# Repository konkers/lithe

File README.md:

# lithe
A joystick/game controller firmware.

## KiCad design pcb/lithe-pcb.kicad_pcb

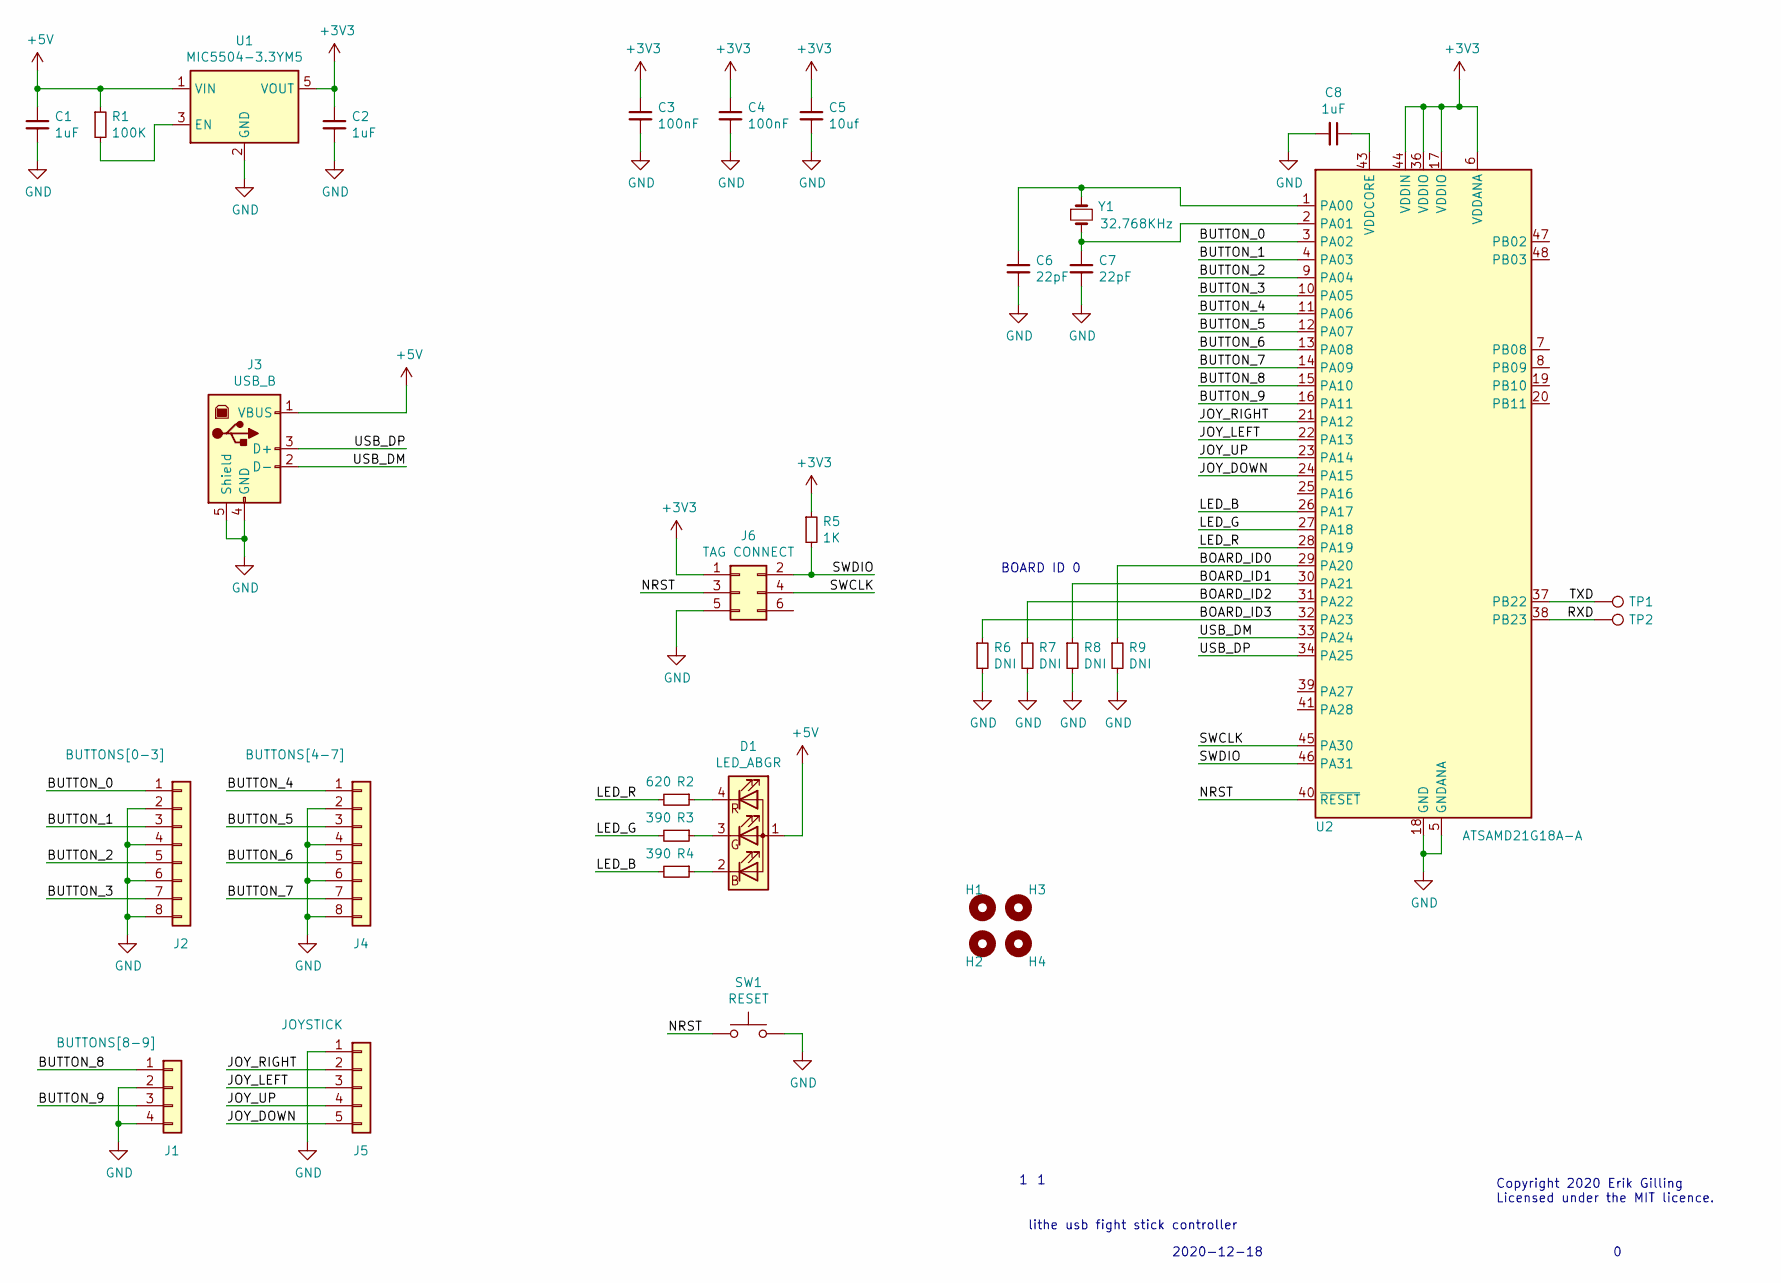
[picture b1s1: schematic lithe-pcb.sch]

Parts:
C1, C2, C8: 1uF; C_0402_1005Metric; DIGI_PN 1276-6524-2-ND
C3, C4: 100nF; C_0402_1005Metric; DIGI_PN 311-2077-1-ND
C5: 10uf; C_0603_1608Metric; DIGI_PN 490-3298-1-ND
C6, C7: 22pF; C_0402_1005Metric; DIGI_PN 445-1239-1-ND
D1: LED_ABGR; LED_Cree-PLCC4_2x2mm_CW; DIGI_PN CLMVC-FKA-CL1D1L71BB7C3C3TR-ND
H1, H2, H3, H4: MountingHole; MountingHole_3.2mm_M3_ISO7380
J1: BUTTONS[8-9]; PhoenixContact_MCV_1,5_4-G-3.5_1x04_P3.50mm_Vertical; DIGI_PN 277-5738-ND
J2: BUTTONS[0-3]; PhoenixContact_MCV_1,5_8-G-3.5_1x08_P3.50mm_Vertical; DIGI_PN 277-5759-ND
J3: USB_B; USB_B_Lumberg_2411_02_Horizontal
J4: BUTTONS[4-7]; PhoenixContact_MCV_1,5_8-G-3.5_1x08_P3.50mm_Vertical; DIGI_PN 277-5759-ND
J5: JOYSTICK; PhoenixContact_MCV_1,5_5-G-3.5_1x05_P3.50mm_Vertical; DIGI_PN 277-5752-ND
J6: TAG CONNECT; Tag-Connect_TC2030-IDC-NL_2x03_P1.27mm_Vertical
R1: 100K; R_0402_1005Metric; DIGI_PN YAG2307TR-ND
R2: 620; R_0402_1005Metric; DIGI_PN 311-620LRTR-ND
R3, R4: 390; R_0402_1005Metric; DIGI_PN 311-390LRTR-ND
R5: 1K; R_0402_1005Metric; DIGI_PN 311-1.00KLRTR-ND
R6, R7, R8, R9: DNI; R_0402_1005Metric; DIGI_PN 311-0.0JRTR-ND
SW1: RESET; SW_SPST_EVQPE1; DIGI_PN CKN12311-2-ND
TP1, TP2: TestPoint; TestPoint_Pad_D1.0mm
U1: MIC5504-3.3YM5; SOT-23-5; DIGI_PN MIC5504-3.3YM5-T5TR-ND
U2: ATSAMD21G18A-A; TQFP-48_7x7mm_P0.5mm; DIGI_PN ATSAMD21G18A-AU-ND
Y1: 32.768KHz; Crystal_SMD_MicroCrystal_CC7V-T1A-2Pin_3.2x1.5mm_HandSolder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; DIGI_PN 2195-CM7VT1ALOWESR32.768KHZ12.5PF20TAQC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

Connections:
+3V3: C2.1, C3.1, C4.1, C5.1, J6.1, R5.1, U1.5 (VOUT), U2.6 (VDDANA), U2.17 (VDDIO), U2.36 (VDDIO), U2.44 (VDDIN)
+5V: C1.1, D1.1 (A), J3.1 (VBUS), R1.1, U1.1 (VIN)
/BOARD_ID0: R9.1, U2.29 (PA20)
/BOARD_ID1: R8.1, U2.30 (PA21)
/BOARD_ID2: R7.1, U2.31 (PA22)
/BOARD_ID3: R6.1, U2.32 (PA23)
/BUTTON_0: J2.1, U2.3 (PA02)
/BUTTON_1: J2.3, U2.4 (PA03)
/BUTTON_2: J2.5, U2.9 (PA04)
/BUTTON_3: J2.7, U2.10 (PA05)
/BUTTON_4: J4.1, U2.11 (PA06)
/BUTTON_5: J4.3, U2.12 (PA07)
/BUTTON_6: J4.5, U2.13 (PA08)
/BUTTON_7: J4.7, U2.14 (PA09)
/BUTTON_8: J1.1, U2.15 (PA10)
/BUTTON_9: J1.3, U2.16 (PA11)
/JOY_DOWN: J5.5, U2.24 (PA15)
/JOY_LEFT: J5.3, U2.22 (PA13)
/JOY_RIGHT: J5.2, U2.21 (PA12)
/JOY_UP: J5.4, U2.23 (PA14)
/LED_B: R4.2, U2.26 (PA17)
/LED_G: R3.2, U2.27 (PA18)
/LED_R: R2.2, U2.28 (PA19)
/NRST: J6.3, SW1.1, U2.40 (~RESET)
/RXD: TP2.1, U2.38 (PB23)
/SWCLK: J6.4, U2.45 (PA30)
/SWDIO: J6.2, R5.2, U2.46 (PA31)
/TXD: TP1.1, U2.37 (PB22)
/USB_DM: J3.2 (D-), U2.33 (PA24)
/USB_DP: J3.3 (D+), U2.34 (PA25)
GND: C1.2, C2.2, C3.2, C4.2, C5.2, C6.2, C7.2, C8.2, J1.2, J1.4, J2.2, J2.4, J2.6, J2.8, J3.4 (GND), J3.5 (Shield), J4.2, J4.4, J4.6, J4.8, J5.1, J6.5, R6.2, R7.2, R8.2, R9.2, SW1.2, U1.2 (GND), U2.5 (GNDANA), U2.18 (GND), U2.35 (GND), U2.42 (GND)
unnamed: C6.1, U2.1 (PA00), Y1.1
unnamed: C7.1, U2.2 (PA01), Y1.2
unnamed: C8.1, U2.43 (VDDCORE)
unnamed: D1.2 (BK), R4.1
unnamed: D1.3 (GK), R3.1
unnamed: D1.4 (RK), R2.1
unnamed: R1.2, U1.3 (EN)

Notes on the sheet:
lithe usb fight stick controller
2020-12-18
Copyright 2020 Erik Gilling Licensed under the MIT licence.
BOARD ID 0

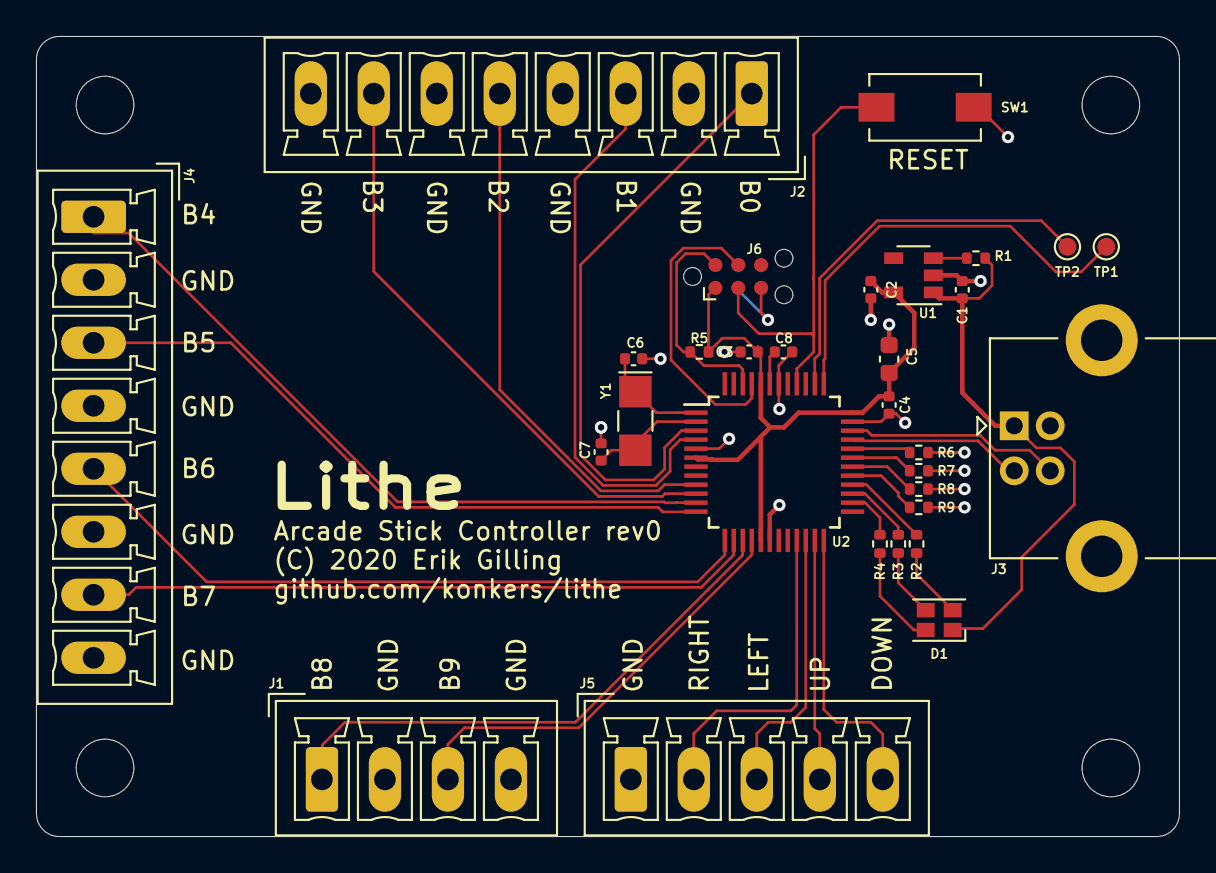
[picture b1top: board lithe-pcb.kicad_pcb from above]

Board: 2 copper layers, 63.5 x 44.5 mm, 34 parts (0 on the bottom side), 38 nets.

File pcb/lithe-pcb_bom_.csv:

Component,Description,Part,References,Value,Footprint,Quantity Per PCB,Datasheet,DIGI_PN
1,"Unpolarized capacitor, small symbol",C_Small,C6 C7,22pF,C_0402_1005Metric,2,~,445-1239-1-ND
2,"Unpolarized capacitor, small symbol",C_Small,C3 C4,100nF,C_0402_1005Metric,2,~,311-2077-1-ND
3,"Unpolarized capacitor, small symbol",C_Small,C1 C2 C8,1uF,C_0402_1005Metric,3,~,1276-6524-2-ND
4,"Unpolarized capacitor, small symbol",C_Small,C5,10uf,C_0603_1608Metric,1,~,490-3298-1-ND
5,"RGB LED, anode/blue/green/red",LED_ABGR,D1,LED_ABGR,LED_Cree-PLCC4_2x2mm_CW,1,~,CLMVC-FKA-CL1D1L71BB7C3C3TR-ND
6,"Generic connector, single row, 01x08, script generated (kicad-library-utils/schlib/autogen/connector/)",Conn_01x08,J2 J4,BUTTONS[0-3],"PhoenixContact_MCV_1,5_8-G-3.5_1x08_P3.50mm_Vertical",2,~,277-5759-ND
7,"Generic connector, single row, 01x04, script generated (kicad-library-utils/schlib/autogen/connector/)",Conn_01x04,J1,BUTTONS[8-9],"PhoenixContact_MCV_1,5_4-G-3.5_1x04_P3.50mm_Vertical",1,~,277-5738-ND
8,"Generic connector, single row, 01x05, script generated (kicad-library-utils/schlib/autogen/connector/)",Conn_01x05,J5,JOYSTICK,"PhoenixContact_MCV_1,5_5-G-3.5_1x05_P3.50mm_Vertical",1,~,277-5752-ND
9,"Generic connector, double row, 02x03, odd/even pin numbering scheme (row 1 odd numbers, row 2 even numbers), script generated (kicad-library-utils/schlib/autogen/connector/)",Conn_02x03_Odd_Even,J6,TAG CONNECT,Tag-Connect_TC2030-IDC-NL_2x03_P1.27mm_Vertical,1,~,
10,USB Type B connector,USB_B,J3,USB_B,USB_B_Lumberg_2411_02_Horizontal,1, ~,
11,"Resistor, small symbol",R_Small,R3 R4,390,R_0402_1005Metric,2,~,311-390LRTR-ND
12,"Resistor, small symbol",R_Small,R2,620,R_0402_1005Metric,1,~,311-620LRTR-ND
13,"Resistor, small symbol",R_Small,R5,1K,R_0402_1005Metric,1,~,311-1.00KLRTR-ND
14,"Resistor, small symbol",R_Small,R1,100K,R_0402_1005Metric,1,~,YAG2307TR-ND
15,"Resistor, small symbol",R_Small,R6 R7 R8 R9,DNI,R_0402_1005Metric,4,~,311-0.0JRTR-ND
16,"Push button switch, generic, two pins",SW_Push,SW1,RESET,SW_SPST_EVQPE1,1,~,CKN12311-2-ND
17,"SAM D21 Microchip SMART ARM-based Flash MCU, 48Mhz, 256K Flash, 32K SRAM, TQFP-48",ATSAMD21G18A-A,U2,ATSAMD21G18A-A,TQFP-48_7x7mm_P0.5mm,1,http://ww1.microchip.com/downloads/en/DeviceDoc/SAM_D21_DA1_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,ATSAMD21G18A-AU-ND
18,"300mA Low-dropout Voltage Regulator, Vout 3.3V, Vin up to 5.5V, SOT-23",MIC5504-3.3YM5,U1,MIC5504-3.3YM5,SOT-23-5,1,http://ww1.microchip.com/downloads/en/DeviceDoc/MIC550X.pdf,MIC5504-3.3YM5-T5TR-ND
19,"Two pin crystal, small symbol",Crystal_Small,Y1,32.768KHz,Crystal_SMD_MicroCrystal_CC7V-T1A-2Pin_3.2x1.5mm_HandSoldering,1,~,2195-CM7VT1ALOWESR32.768KHZ12.5PF20TAQCTR-ND





Component Groups:,19
Component Count:,28
Fitted Components:,28
Number of PCBs:,1
Total components:,28
Schematic Version:,
Schematic Date:,
PCB Variant:,default
BoM Date:,12/20/2020 3:10:21 PM
Schematic Source:,lithe-pcb.sch
KiCad Version:,Eeschema (5.1.8)-1

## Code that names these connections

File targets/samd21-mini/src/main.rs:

#![no_std]
#![no_main]

extern crate atsamd_hal as hal;

use {
    arrayvec::ArrayString,
    core::fmt::{self, Write},
    core::str,
    hal::{
        clock::GenericClockController,
        define_pins,
        gpio::{
            self, Floating, Input, IntoFunction, Pa14, Pa15, Pa16, Pa18, Pa2, Pa20, Pa21, Pa4, Pa6, Pa7, Pa8,
            Pa9, Pb8, Pb9, Port, PullUp, Output, PushPull,
        },
        prelude::*,
        target_device as pac,
        timer::TimerCounter,
        usb::UsbBus,
    },
    lithe,
    rtic::app,
    usb_device::bus::UsbBusAllocator,
};

#[cfg(not(feature = "semihosting"))]
use panic_halt as _;

#[cfg(feature = "semihosting")]
use {
    cortex_m_semihosting::hprintln,
    panic_semihosting as _, // logs messages to the host stderr; requires a debugger
};

define_pins!(
    struct Pins,
    target_device: pac,
    pin joy_right = b8,
    pin joy_left = a2,
    pin joy_up = a4,
    pin joy_down = b9,
    pin button0 = a8,
    pin button1 = a9,
    pin button2 = a14,
    pin button3 = a15,
    pin button4 = a20,
    pin button5 = a21,
    pin button6 = a6,
    pin button7 = a7,
    pin timing_out0 = a18,
    pin timing_out1 = a16,
    pin usb_dm = a24,
    pin usb_dp = a25,
);

#[app(device = hal::target_device, peripherals = true)]
const APP: () = {
    struct Resources {
        usb_bus: &'static UsbBusAllocator<UsbBus>,
        lithe: lithe::Device<'static, UsbBus>,
        timer: TimerCounter<pac::TC4>,
        joy_right: Pb8<Input<PullUp>>,
        joy_left: Pa2<Input<PullUp>>,
        joy_up: Pa4<Input<PullUp>>,
        joy_down: Pb9<Input<PullUp>>,
        button0: Pa8<Input<PullUp>>,
        button1: Pa9<Input<PullUp>>,
        button2: Pa14<Input<PullUp>>,
        button3: Pa15<Input<PullUp>>,
        button4: Pa20<Input<PullUp>>,
        button5: Pa21<Input<PullUp>>,
        button6: Pa6<Input<PullUp>>,
        button7: Pa7<Input<PullUp>>,
        timing_out0: Pa18<Output<PushPull>>,
        timing_out1: Pa16<Output<PushPull>>,
    }

    #[init]
    fn init(ctx: init::Context) -> init::LateResources {
        static mut USB_BUS: Option<UsbBusAllocator<UsbBus>> = None;
        static mut SERIAL: Option<ArrayString<[u8; 64]>> = None;

        // Alias peripherals
        let mut dp: pac::Peripherals = ctx.device;

        let mut clocks = GenericClockController::with_external_32kosc(
            dp.GCLK,
            &mut dp.PM,
            &mut dp.SYSCTRL,
            &mut dp.NVMCTRL,
        );
        let gclk0 = clocks.gclk0();

        let mut pins = Pins::new(dp.PORT);
        let joy_right = pins.joy_right.into_pull_up_input(&mut pins.port);
        let joy_left = pins.joy_left.into_pull_up_input(&mut pins.port);
        let joy_up = pins.joy_up.into_pull_up_input(&mut pins.port);
        let joy_down = pins.joy_down.into_pull_up_input(&mut pins.port);
        let button0 = pins.button0.into_pull_up_input(&mut pins.port);
        let button1 = pins.button1.into_pull_up_input(&mut pins.port);
        let button2 = pins.button2.into_pull_up_input(&mut pins.port);
        let button3 = pins.button3.into_pull_up_input(&mut pins.port);
        let button4 = pins.button4.into_pull_up_input(&mut pins.port);
        let button5 = pins.button5.into_pull_up_input(&mut pins.port);
        let button6 = pins.button6.into_pull_up_input(&mut pins.port);
        let button7 = pins.button7.into_pull_up_input(&mut pins.port);
        let timing_out0 = pins.timing_out0.into_push_pull_output(&mut pins.port);
        let timing_out1 = pins.timing_out1.into_push_pull_output(&mut pins.port);

        let usb_dm = pins.usb_dm.into_function(&mut pins.port);
        let usb_dp = pins.usb_dp.into_function(&mut pins.port);

        let usb_clock = &clocks.usb(&gclk0).unwrap();

        *USB_BUS = Some(UsbBusAllocator::new(UsbBus::new(
            usb_clock, &mut dp.PM, usb_dm, usb_dp, dp.USB,
        )));

        let (serial0, serial1, serial2, serial3) = unsafe {
            let serial0: *const u32 = 0x0080A00C as *const u32;
            let serial1: *const u32 = 0x0080A040 as *const u32;
            let serial2: *const u32 = 0x0080A044 as *const u32;
            let serial3: *const u32 = 0x0080A048 as *const u32;
            (*serial0, *serial1, *serial2, *serial3)
        };
        *SERIAL = Some(ArrayString::new());
        write!(
            SERIAL.as_mut().unwrap(),
            "{:08X}{:08X}{:08X}{:08X}",
            serial0,
            serial1,
            serial2,
            serial3
        )
        .unwrap();

        #[cfg(feature = "semihosting")]
        hprintln!("Preparing HID mouse...").unwrap();
        let lithe = lithe::Device::new(USB_BUS.as_ref().unwrap(), SERIAL.as_ref().unwrap());

        #[cfg(feature = "semihosting")]
        hprintln!("Setting up timer...").unwrap();
        // gclk0 represents a configured clock using the system 48MHz oscillator
        // configure a clock for the TC4 and TC5 peripherals
        let tc45 = &clocks.tc4_tc5(&gclk0).unwrap();
        // instantiate a timer objec for the TC4 peripheral
        let mut timer = TimerCounter::tc4_(tc45, dp.TC4, &mut dp.PM);
        timer.start(10.khz());
        timer.enable_interrupt();

        #[cfg(feature = "semihosting")]
        hprintln!("Defining late resources...").unwrap();
        init::LateResources {
            usb_bus: USB_BUS.as_ref().unwrap(),
            lithe,
            timer,
            joy_right,
            joy_left,
            joy_up,
            joy_down,
            button0,
            button1,
            button2,
            button3,
            button4,
            button5,
            button6,
            button7,
            timing_out0,
            timing_out1,
        }
    }

    #[task(binds = TC4, resources = [button0, button1, button2, 
        button3, button4, button5, button6, button7, joy_right, 
        joy_left, joy_up, joy_down, lithe, timing_out0, timer])]
    fn tc4_handler(ctx: tc4_handler::Context) {
        ctx.resources.timing_out0.set_high().ok();
        let pins = lithe::PinState {
            joy_right: ctx.resources.joy_right.is_low().unwrap(),
            joy_left: ctx.resources.joy_left.is_low().unwrap(),
            joy_up: ctx.resources.joy_up.is_low().unwrap(),
            joy_down: ctx.resources.joy_down.is_low().unwrap(),
            buttons: [
                ctx.resources.button0.is_low().unwrap(),
                ctx.resources.button1.is_low().unwrap(),
                ctx.resources.button2.is_low().unwrap(),
                ctx.resources.button3.is_low().unwrap(),
                ctx.resources.button4.is_low().unwrap(),
                ctx.resources.button5.is_low().unwrap(),
                ctx.resources.button6.is_low().unwrap(),
                ctx.resources.button7.is_low().unwrap(),
                false,
                false,
            ],
        };
        //   rprintln!("t: {:?}", &pins);
        ctx.resources.lithe.process_pins(&pins);
        ctx.resources.timer.wait().ok();
        ctx.resources.timing_out0.set_low().ok();
    }

    #[task(binds = USB, resources = [lithe, timing_out1])]
    fn usb_handler(ctx: usb_handler::Context) {
        ctx.resources.timing_out1.set_high().ok();
        ctx.resources.lithe.usb_poll();
        ctx.resources.timing_out1.set_low().ok();
    }
};

pub struct ByteMutWriter<'a> {
    pub buf: &'a mut [u8],
    pub cursor: usize,
}

impl<'a> ByteMutWriter<'a> {
    pub fn new(buf: &'a mut [u8]) -> Self {
        ByteMutWriter { buf, cursor: 0 }
    }

    pub fn as_str(&self) -> &str {
        str::from_utf8(&self.buf[0..self.cursor]).unwrap()
    }

    #[inline]
    pub fn capacity(&self) -> usize {
        self.buf.len()
    }

    pub fn clear(&mut self) {
        self.cursor = 0;
    }

    pub fn len(&self) -> usize {
        self.cursor
    }

    pub fn empty(&self) -> bool {
        self.cursor == 0
    }

    pub fn full(&self) -> bool {
        self.capacity() == self.cursor
    }
}

impl fmt::Write for ByteMutWriter<'_> {
    fn write_str(&mut self, s: &str) -> fmt::Result {
        let cap = self.capacity();
        for (i, &b) in self.buf[self.cursor..cap]
            .iter_mut()
            .zip(s.as_bytes().iter())
        {
            *i = b;
        }
        self.cursor = usize::min(cap, self.cursor + s.as_bytes().len());
        Ok(())
    }
}

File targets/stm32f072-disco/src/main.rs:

#![no_std]
#![no_main]

use {
    cortex_m::interrupt::free as disable_interrupts,
    lithe,
    rtic::app,
    stm32f0xx_hal::{
        gpio::gpioc::{PC10, PC11, PC12, PC13},
        gpio::{Input, PullUp},
        pac,
        prelude::*,
        time::KiloHertz,
        timers::{Event, Timer},
        usb,
    },
    usb_device::bus::UsbBusAllocator,
};

#[cfg(not(feature = "semihosting"))]
use panic_halt as _;

#[cfg(feature = "semihosting")]
use {
    cortex_m_semihosting::hprintln,
    panic_semihosting as _, // logs messages to the host stderr; requires a debugger
};

#[app(device = stm32f0xx_hal::pac, peripherals = true)]
const APP: () = {
    struct Resources {
        usb_bus: &'static UsbBusAllocator<usb::UsbBusType>,
        lithe: lithe::Device<'static, usb::UsbBusType>,
        timer: Timer<pac::TIM7>,
        joy_right: PC10<Input<PullUp>>,
        joy_left: PC11<Input<PullUp>>,
        joy_up: PC12<Input<PullUp>>,
        joy_down: PC13<Input<PullUp>>,
    }

    #[init]
    fn init(ctx: init::Context) -> init::LateResources {
        static mut USB_BUS: Option<UsbBusAllocator<usb::UsbBusType>> = None;

        // Alias peripherals
        let mut dp: pac::Peripherals = ctx.device;

        // This enables clock for SYSCFG and remaps USB pins to PA9 and PA10.
        usb::remap_pins(&mut dp.RCC, &mut dp.SYSCFG);

        #[cfg(feature = "semihosting")]
        hprintln!("Initializing peripherals").unwrap();
        let mut rcc = dp
            .RCC
            .configure()
            .usbsrc(stm32f0xx_hal::rcc::USBClockSource::HSI48)
            .hsi48()
            .enable_crs(dp.CRS)
            .sysclk(48.mhz())
            .pclk(24.mhz())
            .freeze(&mut dp.FLASH);

        // User Button and USB
        let gpioa = dp.GPIOA.split(&mut rcc);
        let gpioc = dp.GPIOC.split(&mut rcc);
        let (usb_dm, usb_dp, joy_right, joy_left, joy_up, joy_down) = disable_interrupts(|cs| {
            (
                gpioa.pa11,
                gpioa.pa12,
                gpioc.pc10.into_pull_up_input(cs),
                gpioc.pc11.into_pull_up_input(cs),
                gpioc.pc12.into_pull_up_input(cs),
                gpioc.pc13.into_pull_up_input(cs),
            )
        });

        let usb = usb::Peripheral {
            usb: dp.USB,
            pin_dm: usb_dm,
            pin_dp: usb_dp,
        };
        *USB_BUS = Some(usb::UsbBus::new(usb));

        let lithe = lithe::Device::new(USB_BUS.as_ref().unwrap(), &"12345");

        #[cfg(feature = "semihosting")]
        hprintln!("Setting up timer...").unwrap();
        let mut timer = Timer::tim7(dp.TIM7, KiloHertz(2), &mut rcc);
        timer.listen(Event::TimeOut);

        #[cfg(feature = "semihosting")]
        hprintln!("Defining late resources...").unwrap();
        init::LateResources {
            usb_bus: USB_BUS.as_ref().unwrap(),
            lithe,
            timer,
            joy_right,
            joy_left,
            joy_up,
            joy_down,
        }
    }

    #[task(binds = TIM7, resources = [joy_right, joy_left, joy_up, joy_down, lithe, timer])]
    fn tim7_handler(ctx: tim7_handler::Context) {
        let pins = lithe::PinState {
            joy_right: ctx.resources.joy_right.is_low().unwrap(),
            joy_left: ctx.resources.joy_left.is_low().unwrap(),
            joy_up: ctx.resources.joy_up.is_low().unwrap(),
            joy_down: ctx.resources.joy_down.is_low().unwrap(),
            buttons: [false; 10],
        };
        ctx.resources.lithe.process_pins(&pins);
        ctx.resources.timer.wait().ok();
    }

    #[task(binds = USB, resources = [lithe])]
    fn usb_handler(ctx: usb_handler::Context) {
        ctx.resources.lithe.usb_poll();
    }
};

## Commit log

2020-12-08 Add stub stm32f071-disco target
2020-12-09 Prototype of USB joystick.
2020-12-14 Add samd21 prototype.
2020-12-14 dos2unix Cargo.toml
2020-12-16 Move common code to lithe library.
    - Extract pin interpretation and USB device into lithe library.
    - Update samd21-mini to use lithe library.
    - Add buttons to samd21-mini.
    - Fix pin definitions for samd21-mini.
2020-12-16 Update stm32f072-disco to use lithe library
    Untested on HW.
2020-12-18 WIP: hardware
2020-12-19 [pcb] Add rev0 of PCB.
2020-12-20 [samd21] Increase polling frequency to 10KHz.
    Verified ample overhead through scope tracing.
2020-12-20 [samd21] Add scope trace outputs.
    Add gpio outputs to signal when the timer and usb interrupts are
    active. This can be used to inspect timmings on an oscilliscope.
2020-12-20 [lithe] Use allocated VID/PID from pid.codes.
    https://pid.codes/1209/EEEE/
2020-12-20 [pcb] Annoate parts with DigiKey P/Ns and add BOM.

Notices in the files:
pcb/lithe-pcb.kicad_pcb:
(C) 2020 Erik Gilling
